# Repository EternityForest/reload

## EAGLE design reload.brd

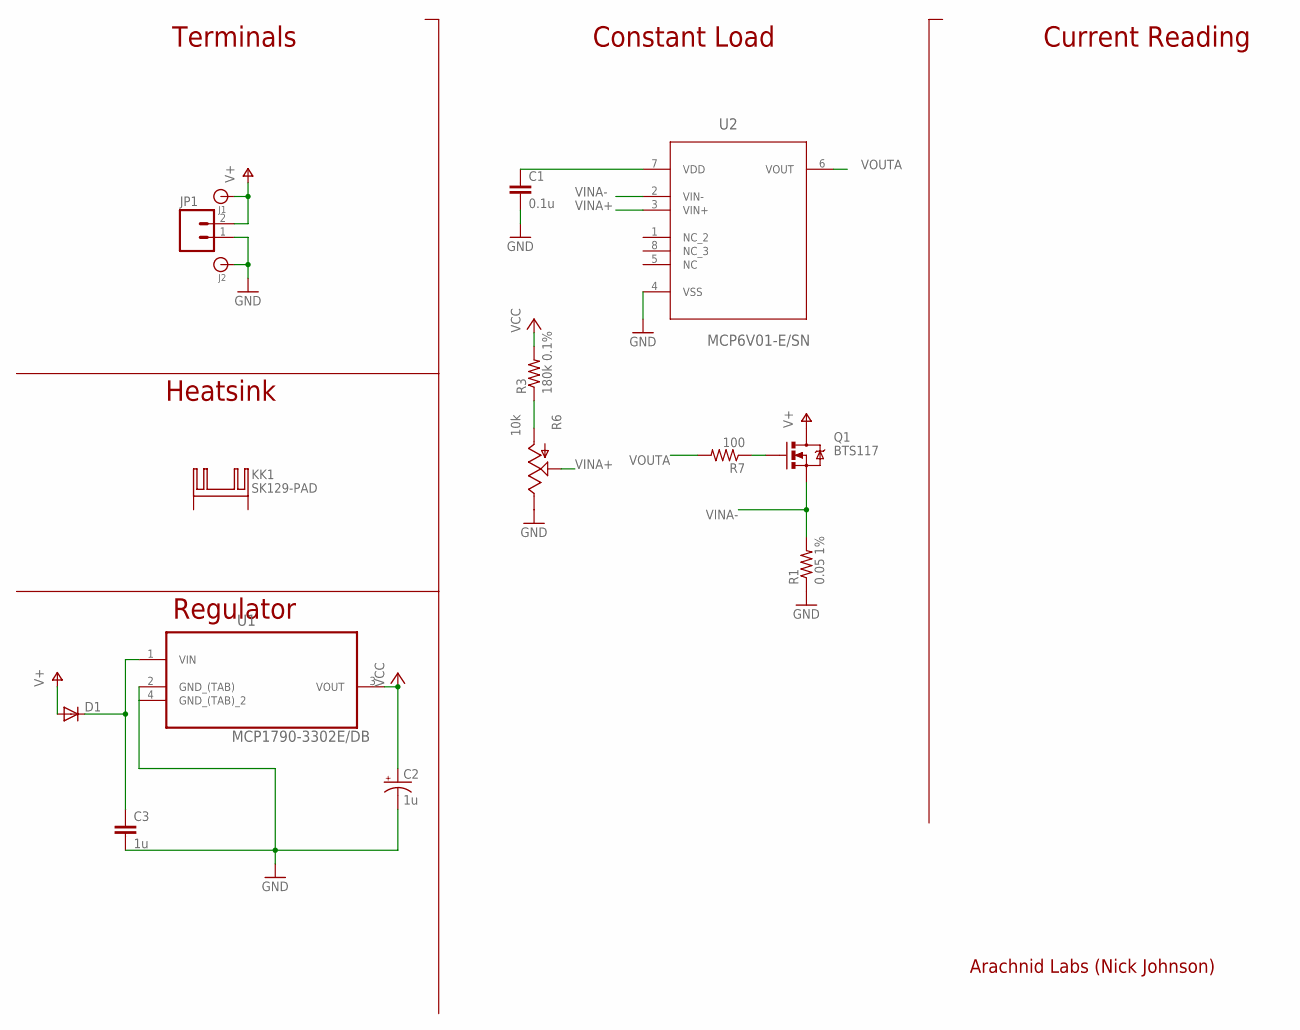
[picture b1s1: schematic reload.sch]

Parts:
C1: 0.1u; CAP-PTH-SMALL
C2: 1u; CPOL-RADIAL-10UF-25V
C3: 1u; CAP-PTH-5MM
D1: DIODE1N4148; DIODE-1N4148
J1, J2: BANANA_CONN
JP1: M02; SPRINGTERMINAL-5MM-2
KK1: SK129-PAD; SK129
Q1: BTS117; TO220V
R1: 0.05 1%; AXIAL-0.6
R3: 180k 0.1%; AXIAL-0.3
R6: 10k; ALPS_POT
R7: 100; AXIAL-0.3
U1: MCP1790-3302E/DB; SOT230P700X180-4N
U2: MCP6V01-E/SN; SOIC127P600X175-8N

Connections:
GND: C1.2, C2.2 (-), C3.2, J2.P$1, JP1.1, R1.P$1 (1), R6.P$1 (E), U1.2 (GND_(TAB)), U1.4 (GND_(TAB)_2), U2.4 (VSS)
unnamed: R3.P$1 (1), R6.P$3 (A)
unnamed: C1.1, U2.7 (VDD)
unnamed: C3.1, D1.C, U1.1 (VIN)
unnamed: Q1.1 (G), R7.P$1 (1)
V+: D1.A, J1.P$1, JP1.2, Q1.2 (D)
VCC: C2.1 (+), R3.P$2 (2)
VINA+: R6.P$2 (S), U2.3 (VIN+)
VINA-: Q1.3 (S), R1.P$2 (2), U2.2 (VIN-)
VOUTA: R7.P$2 (2), U2.6 (VOUT)

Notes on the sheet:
Terminals
Heatsink
Regulator
Constant Load
Current Reading
Arachnid Labs (Nick Johnson)

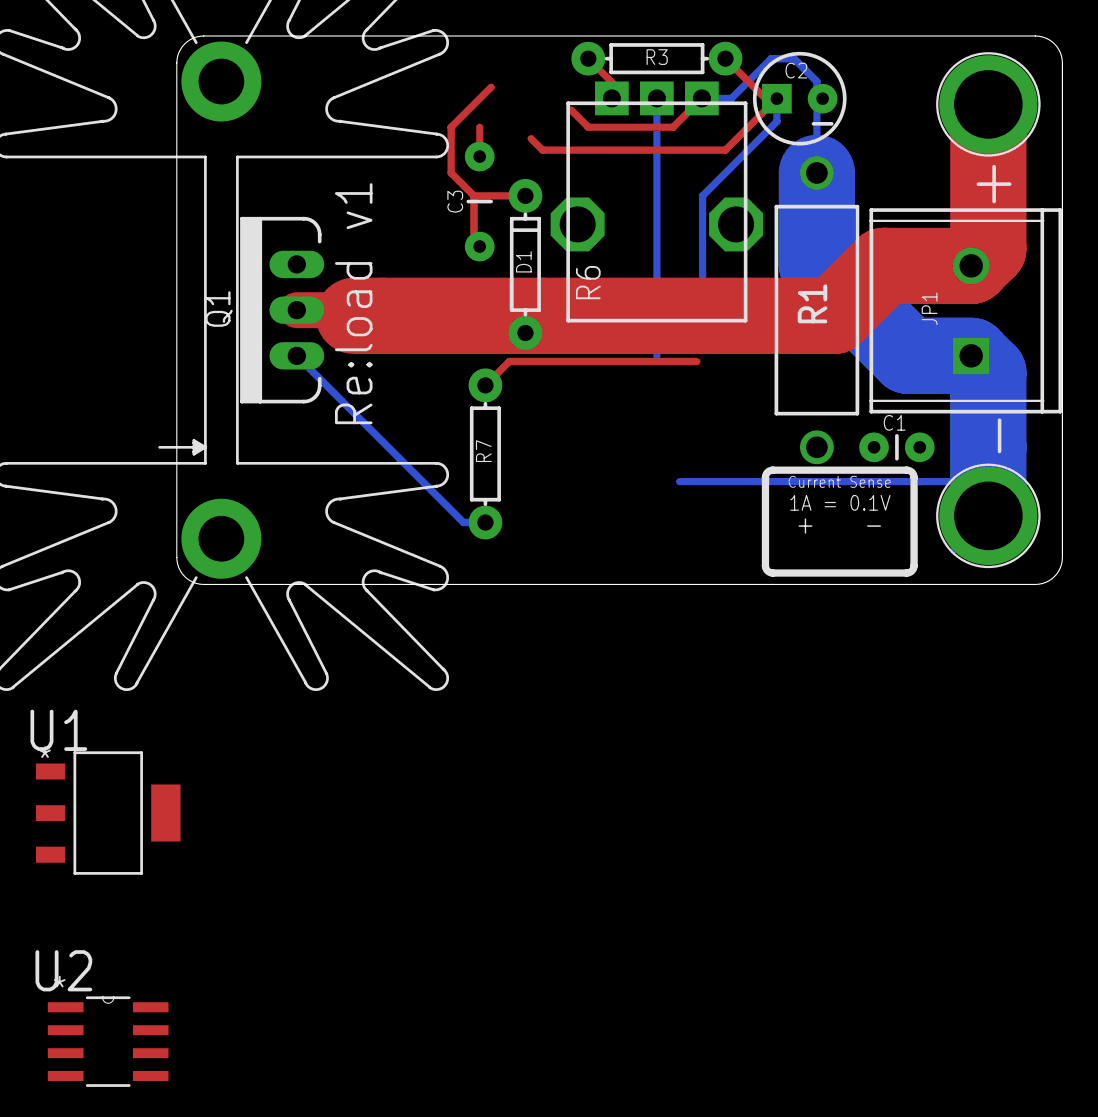
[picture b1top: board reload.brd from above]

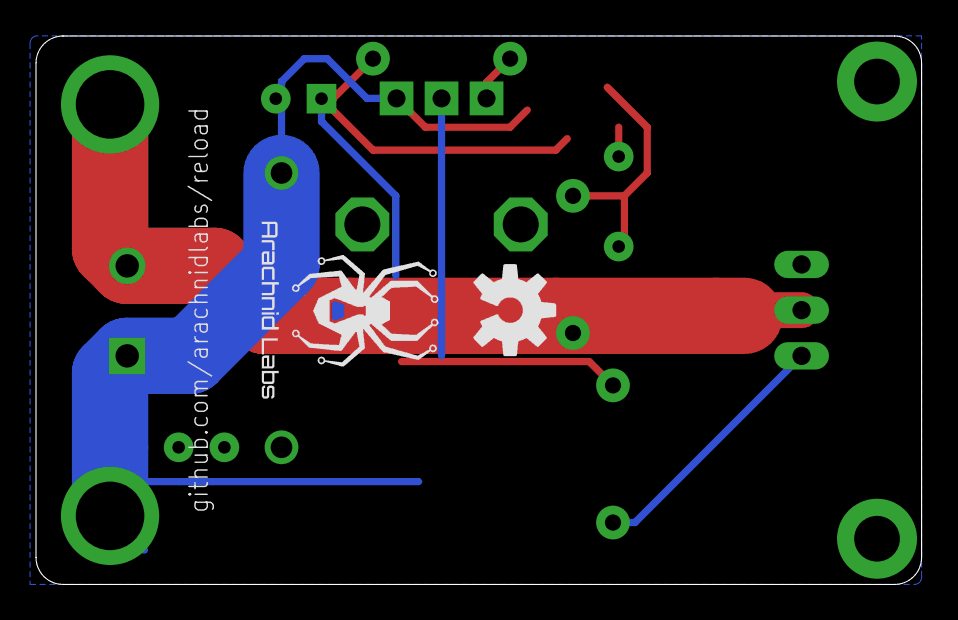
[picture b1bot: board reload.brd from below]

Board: 2 copper layers, 49.2 x 30.5 mm, 17 parts (2 on the bottom side), 10 nets.

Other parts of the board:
U$2: ARACHNID_LABS_LOGO_SM
U$3: OSHW-LOGO-M

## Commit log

2013-02-15 Started modding. Still need to add chips.

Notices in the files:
parts and their libraries:
SparkFun-Passives: Licensing: CC v3.0 Share-Alike You are welcome to use this library for commercial purposes.
SparkFun-Aesthetics: Released under the Creative Commons
SparkFun-Aesthetics: http://creativecommons.org/licenses/by-sa/3.0
